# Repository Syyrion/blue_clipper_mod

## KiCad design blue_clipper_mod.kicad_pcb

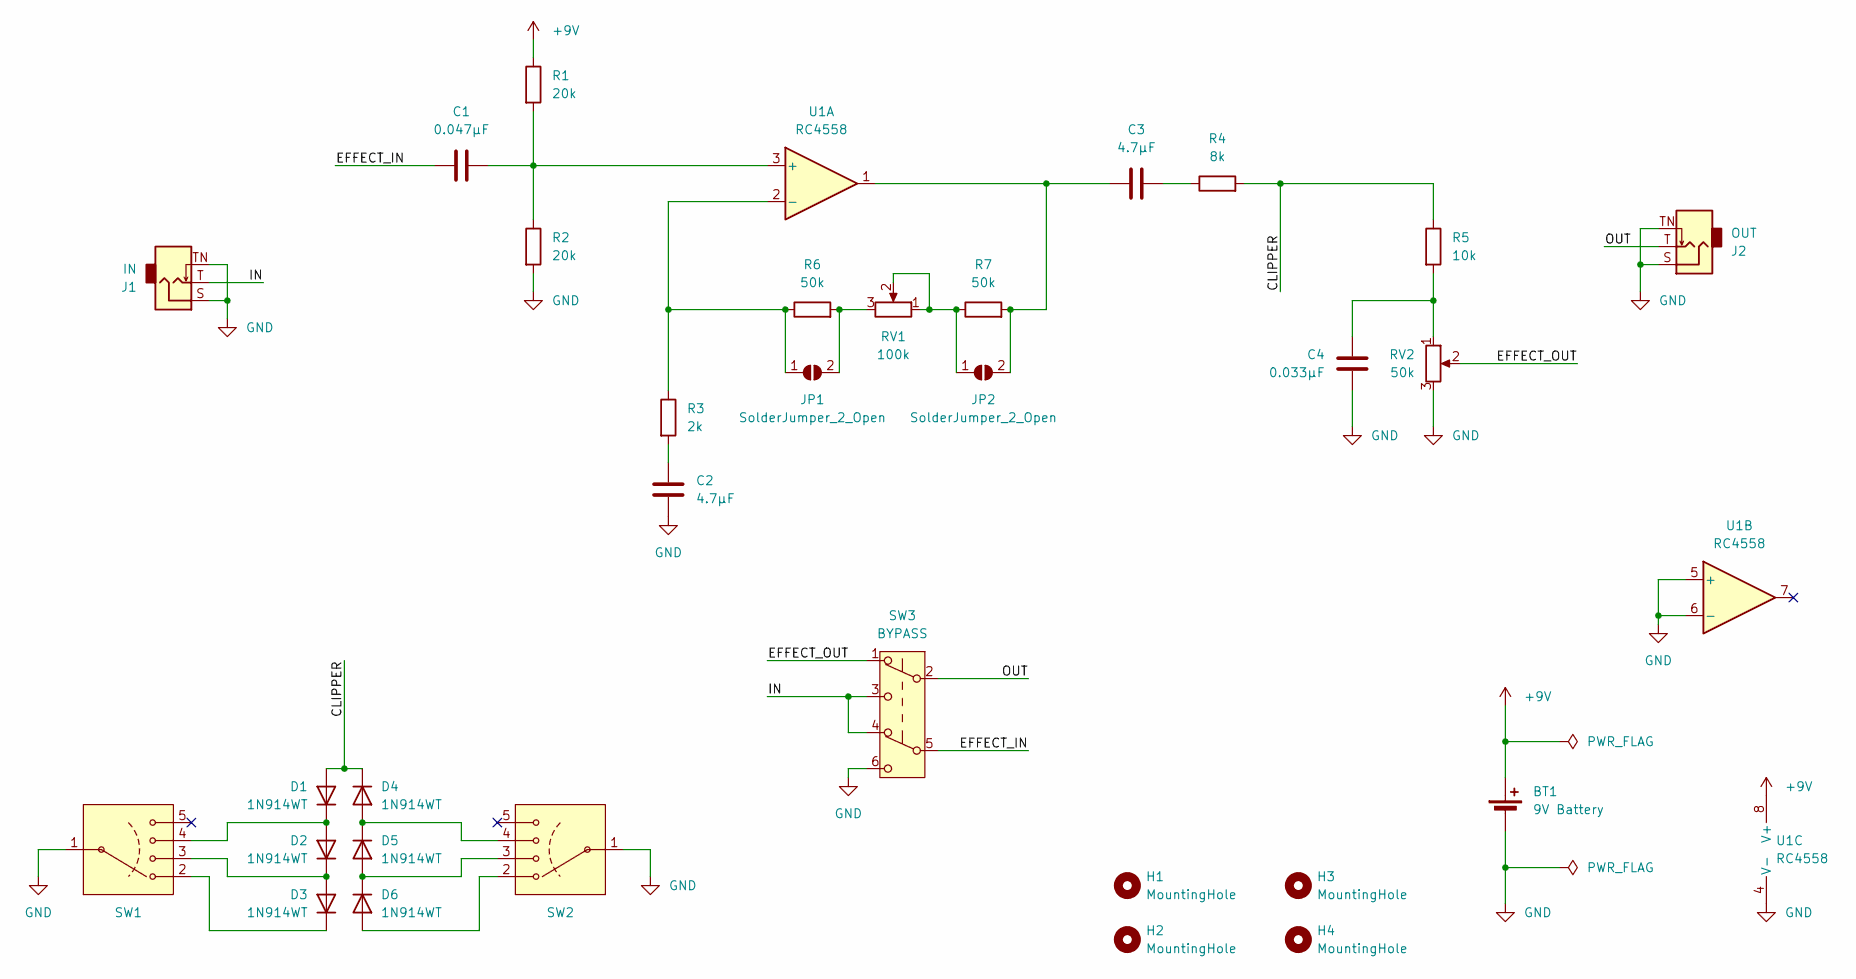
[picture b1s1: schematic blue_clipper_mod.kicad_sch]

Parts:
BT1: 9V Battery; PinHeader_1x02_P2.54mm_Vertical
C1: 0.047µF; C_0603_1608Metric
C2, C3: 4.7µF; CP_Radial_D4.0mm_P1.50mm
C4: 0.033µF; C_0603_1608Metric_Pad1.08x0.95mm_HandSolder
D1, D2, D3, D4, D5, D6: 1N914WT; D_SOD-523
H1, H2, H3, H4: MountingHole; MountingHole_3.2mm_M3
J1: IN; jack_pads
J2: OUT; jack_pads
JP1, JP2: SolderJumper_2_Open; SolderJumper-2_P1.3mm_Open_RoundedPad1.0x1.5mm
R1, R2: 20k; R_0603_1608Metric_Pad0.98x0.95mm_HandSolder
R3: 2k; R_0603_1608Metric_Pad0.98x0.95mm_HandSolder
R4: 8k; R_0603_1608Metric_Pad0.98x0.95mm_HandSolder
R5: 10k; R_0603_1608Metric_Pad0.98x0.95mm_HandSolder
R6, R7: 50k; R_0603_1608Metric_Pad0.98x0.95mm_HandSolder
RV1: 100k; PinHeader_1x03_P2.54mm_Vertical
RV2: 50k; PinHeader_1x03_P2.54mm_Vertical
SW1, SW2: PinHeader_1x05_P2.54mm_Vertical
SW3: BYPASS; PinHeader_1x06_P2.54mm_Vertical
U1: RC4558; DIP-8_W7.62mm_Socket

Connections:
+9V: BT1.1 (+), R1.1, U1.8 (V+)
/CLIPPER: D1.2 (A), D4.1 (K), R4.2, R5.1
/EFFECT_IN: C1.1, SW3.5 (B)
/EFFECT_OUT: RV2.2, SW3.1 (A)
/IN: J1.T, SW3.3 (C), SW3.4 (A)
/OUT: J2.T, SW3.2 (B)
GND: BT1.2 (-), C2.2, C4.2, J1.S, J1.TN, J2.S, J2.TN, R2.2, RV2.3, SW1.1, SW2.1, SW3.6 (C), U1.4 (V-), U1.5 (+), U1.6 (-)
unnamed: C2.1, R3.2
unnamed: C3.2, R4.1
unnamed: C4.1, R5.2, RV2.1
unnamed: D1.1 (K), D2.2 (A), SW1.4
unnamed: D2.1 (K), D3.2 (A), SW1.3
unnamed: D3.1 (K), SW1.2
unnamed: D4.2 (A), D5.1 (K), SW2.4
unnamed: D5.2 (A), D6.1 (K), SW2.3
unnamed: D6.2 (A), SW2.2
unnamed: JP1.1 (A), R3.1, R6.1, U1.2 (-)
unnamed: JP1.2 (B), R6.2, RV1.3
unnamed: JP2.1 (A), R7.1, RV1.1, RV1.2
unnamed: C3.1, JP2.2 (B), R7.2, U1.1
unnamed: C1.2, R1.2, R2.1, U1.3 (+)

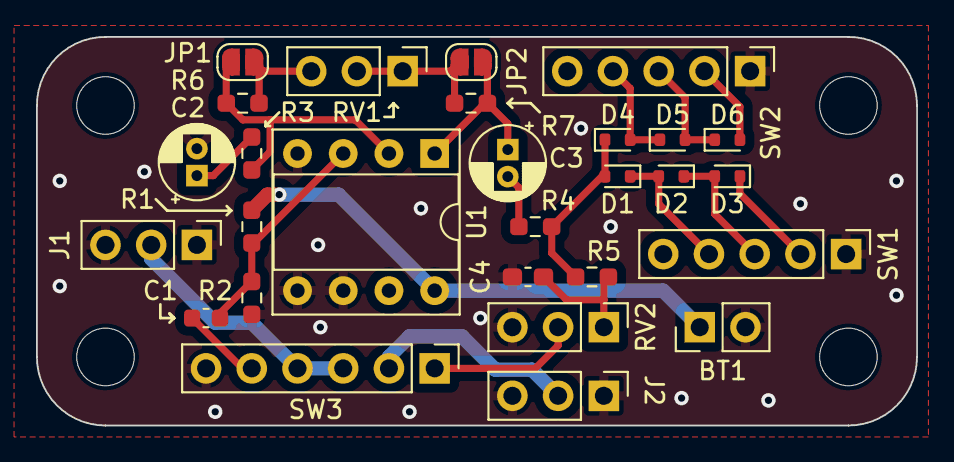
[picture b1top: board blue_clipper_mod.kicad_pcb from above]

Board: 2 copper layers, 48.9 x 21.6 mm, 32 parts (0 on the bottom side), 21 nets.

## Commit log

2024-02-18 add clipper
2024-02-21 add gitignore
2024-02-21 Clean Up schematic
2024-02-22 schematic probably good - round tracks fully necessary
2024-02-22 dangit one of the diodes was flipped the wrong way
2024-02-22 reran autoroute
2024-02-22 Revert "reran autoroute"
    This reverts commit 381ba4100bb96fee684d495079d12acf929bcbfa.
2024-02-22 fix everything
2024-02-26 Get majorly carried away
2024-02-26 add new files
